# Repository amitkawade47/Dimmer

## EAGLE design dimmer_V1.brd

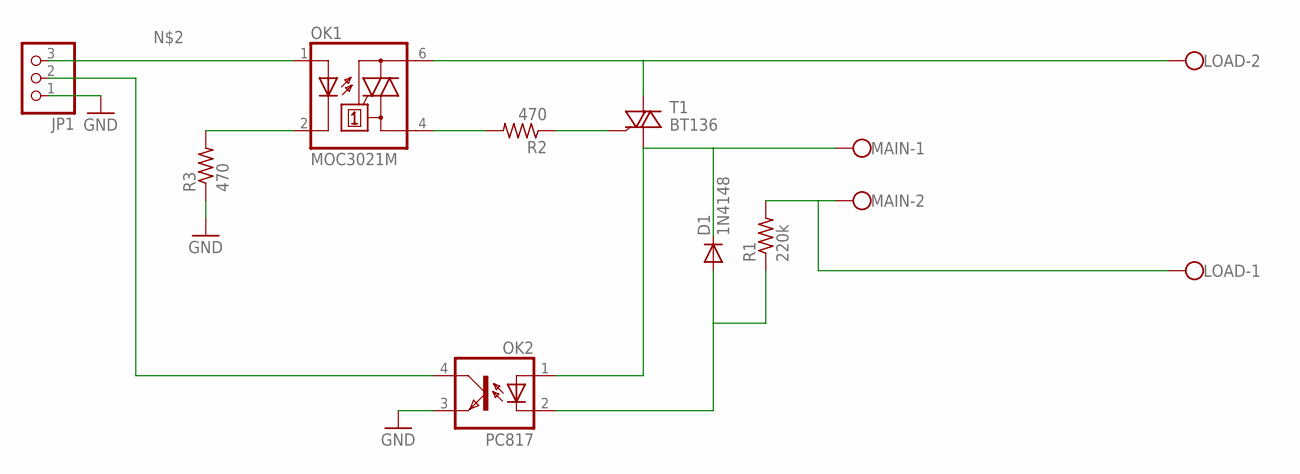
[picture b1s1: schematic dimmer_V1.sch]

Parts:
D1: 1N4148; DO41-10
JP1: PINHD-1X3; 1X03
LOAD: W237-102
MAIN: W237-102
OK1: MOC3021M; DIL06
OK2: PC817; DIL04
R1: 220k; 0207/10
R2, R3: 470; 0207/10
T1: BT136; TO220AB

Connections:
GND: JP1.1, OK2.3 (EMIT), R3.1
unnamed: OK1.2 (C), R3.2
unnamed: JP1.3, OK1.1 (A)
unnamed: OK1.4 (A1), R2.2
unnamed: R2.1, T1.3 (G)
unnamed: LOAD.2, OK1.6 (A2), T1.2 (A2)
unnamed: D1.C, MAIN.1, OK2.1 (A), T1.1 (A1)
unnamed: LOAD.1, MAIN.2, R1.2
unnamed: D1.A, OK2.2 (C), R1.1
unnamed: JP1.2, OK2.4 (COL)

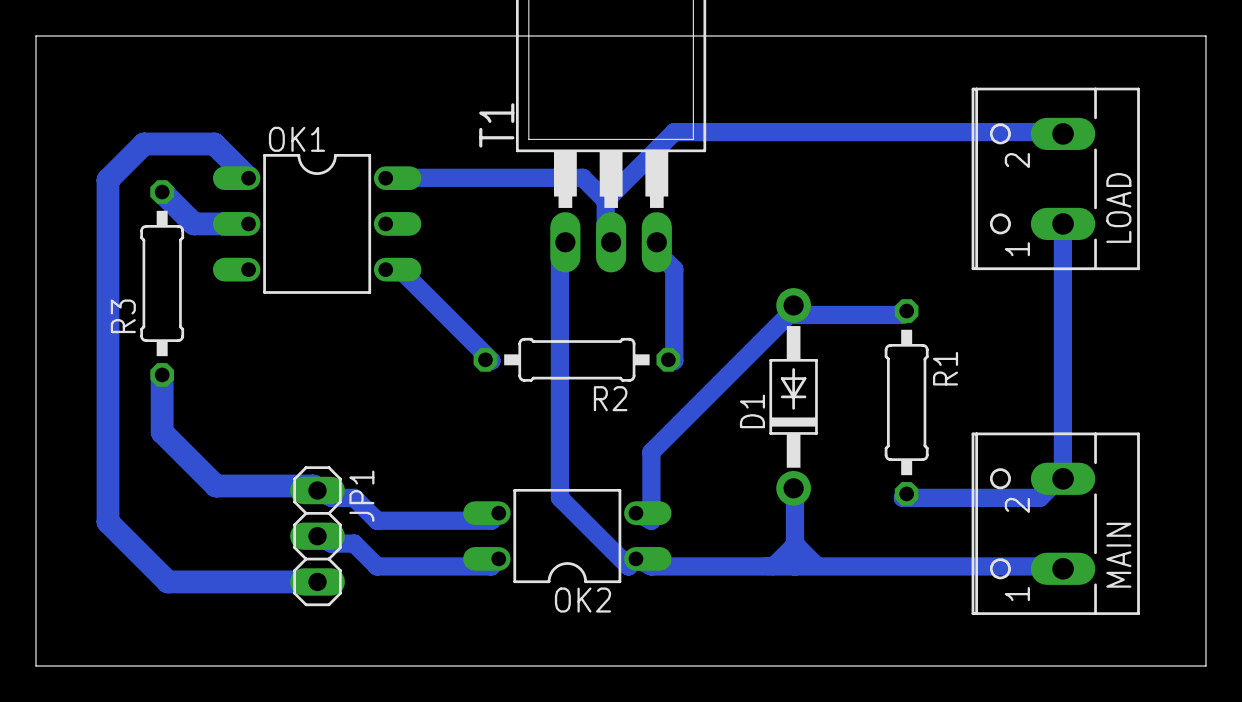
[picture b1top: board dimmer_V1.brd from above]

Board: 2 copper layers, 65.0 x 35.0 mm, 10 parts (0 on the bottom side), 10 nets.

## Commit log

2018-02-17 Using MOC3021,PC817
    source link of schematic: http://alfadex.com/2014/02/dimming-230v-ac-with-arduino-2/

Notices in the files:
parts and their libraries:
SparkFun-Aesthetics: Licensing: Creative Commons ShareAlike 4.0 International - https://creativecommons.org/licenses/by-sa/4.0
